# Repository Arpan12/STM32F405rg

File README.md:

a STM32 based board designed in Kicad. Have support for UART,I2C. Firmware can be uploaded using SWD pin. Support for debugging using SWO. Can be powered by 12v or 5v USB.

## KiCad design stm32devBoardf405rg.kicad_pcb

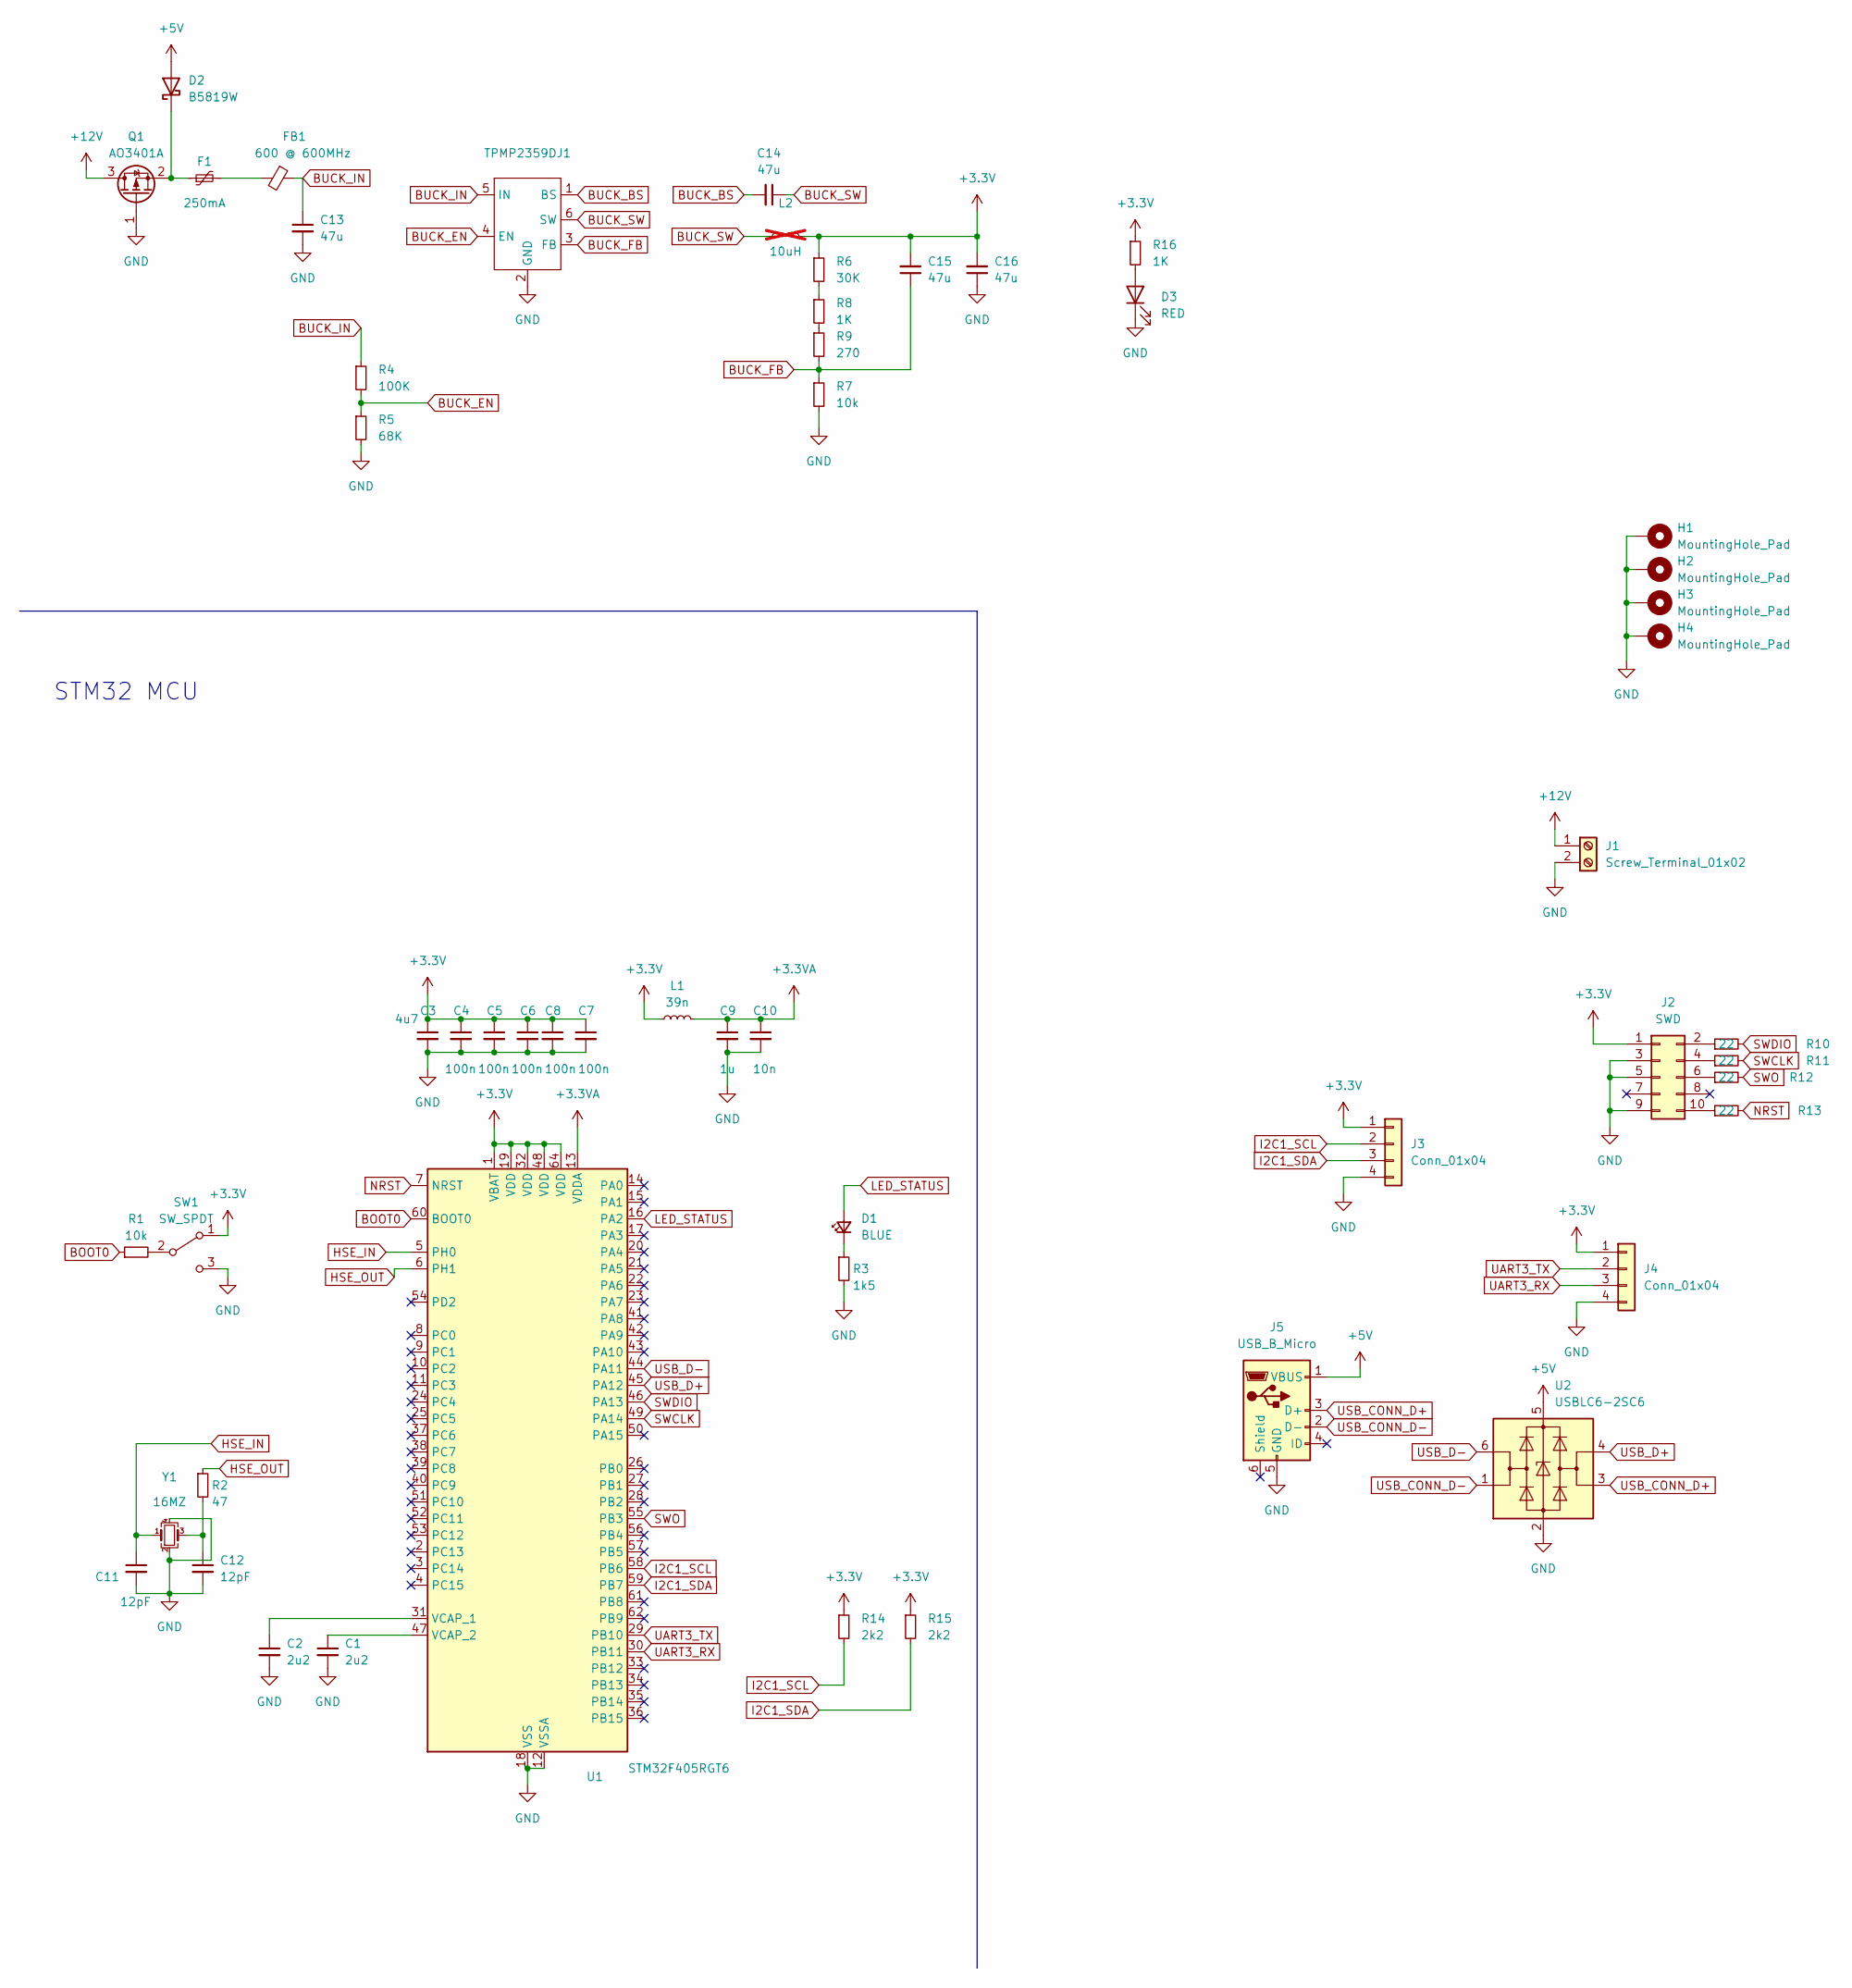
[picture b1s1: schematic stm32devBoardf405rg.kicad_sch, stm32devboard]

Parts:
C1, C2: 2u2; C_0603_1608Metric; LCSC Part# C23630
C3: 4u7; C_0603_1608Metric; LCSC Part# C19666
C4, C5, C6, C7, C8: 100n; C_0402_1005Metric; LCSC Part# C1525
C9: 1u; C_0402_1005Metric; LCSC Part# C52923
C10: 10n; C_0402_1005Metric; LCSC Part# C15195
C11, C12: 12pF; C_0402_1005Metric; LCSC Part# C1547
C13, C14, C15, C16: 47u; C_0603_1608Metric; LCSC Part# C178330
D1: BLUE; LED_0603_1608Metric; LCSC Part# C72041
D2: B5819W; D_SOD-123; LCSC Part# C8598
D3: RED; LED_0603_1608Metric; LCSC Part# C2286
F1: 250mA; Fuse_1206_3216Metric; LCSC Part# C369159
FB1: 600 @ 600MHz; L_0805_2012Metric; LCSC Part# C1017
H1, H2, H3, H4: MountingHole_Pad; MountingHole_4.3mm_M4_Pad_Via
J1: Screw_Terminal_01x02; TerminalBlock_Phoenix_PT-1,5-2-3.5-H_1x02_P3.50mm_Horizontal
J2: SWD; PinHeader_2x05_P1.27mm_Vertical_SMD
J3, J4: Conn_01x04; Molex_PicoBlade_53048-0410_1x04_P1.25mm_Horizontal
J5: USB_B_Micro; USB_Micro-B_Amphenol_10103594-0001LF_Horizontal
L1: 39n; C_0402_1005Metric; LCSC Part# C26443
L2: 10uH; L_Sunlord_MWSA0503S; LCSC Part# C139506; not fitted
Q1: AO3401A; SOT-23; LCSC Part# C15127
R1: 10k; R_0402_1005Metric; LCSC Part# C25744
R2: 47; R_0402_1005Metric; LCSC Part# C25118
R3: 1k5; R_0603_1608Metric; LCSC Part# C22843
R4: 100K; R_0603_1608Metric; LCSC Part# C25803
R5: 68K; R_0603_1608Metric; LCSC Part# C23231
R6: 30K; R_0603_1608Metric; LCSC Part# C22984
R7: 10k; R_0603_1608Metric; LCSC Part# C25804
R8, R16: 1K; R_0603_1608Metric; LCSC Part# C21190
R9: 270; R_0603_1608Metric; LCSC Part# C22966
R10, R11, R12, R13: 22; R_0603_1608Metric; LCSC Part# C23345
R14, R15: 2k2; R_0402_1005Metric; LCSC Part# C25879
SW1: SW_SPDT; SW_SPDT_PCM12
TPMP2359DJ1: SOT-23-6; LCSC Part# C2959845
U1: STM32F405RGT6; LQFP-64_10x10mm_P0.5mm; LCSC Part# C15742
U2: USBLC6-2SC6; SOT-23-6; LCSC Part# C7519
Y1: 16MZ; Crystal_SMD_3225-4Pin_3.2x2.5mm; LCSC Part# C13738

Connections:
+3.3V: C3.1, C4.1, C5.1, C6.1, C7.1, C8.1, C15.2, C16.2, J2.1, J3.1, J4.1, L1.1, L2.2, R6.1, R14.1, R15.1, R16.1, SW1.1 (A), U1.1 (VBAT), U1.19 (VDD), U1.32 (VDD), U1.48 (VDD), U1.64 (VDD)
+3.3VA: C9.1, C10.1, L1.2, U1.13 (VDDA)
+5V: D2.2 (A), J5.1 (VBUS), U2.5 (VBUS)
+12V: J1.1, Q1.3 (D)
BOOT0: R1.1, U1.60 (BOOT0)
BUCK_BS: C14.2, TPMP2359DJ1.1 (BS)
BUCK_EN: R4.2, R5.1, TPMP2359DJ1.4 (EN)
BUCK_FB: C15.1, R7.1, R9.2, TPMP2359DJ1.3 (FB)
BUCK_IN: C13.1, FB1.1, R4.1, TPMP2359DJ1.5 (IN)
BUCK_SW: C14.1, L2.1, TPMP2359DJ1.6 (SW)
GND: C1.2, C2.2, C3.2, C4.2, C5.2, C6.2, C7.2, C8.2, C9.2, C10.2, C11.2, C12.2, C13.2, C16.1, D3.1 (K), H1.1, H2.1, H3.1, H4.1, J1.2, J2.3, J2.5, J2.9, J3.4, J4.4, J5.5 (GND), Q1.1 (G), R3.2, R5.2, R7.2, SW1.3 (C), TPMP2359DJ1.2 (GND), U1.12 (VSSA), U1.18 (VSS), U1.63 (VSS), U2.2 (GND), Y1.2, Y1.4
HSE_IN: C11.1, U1.5 (PH0), Y1.1
HSE_OUT: R2.1, U1.6 (PH1)
I2C1_SCL: J3.2, R14.2, U1.58 (PB6)
I2C1_SDA: J3.3, R15.2, U1.59 (PB7)
LED_STATUS: D1.2 (A), U1.16 (PA2)
NRST: R13.2, U1.7 (NRST)
unnamed: C12.1, R2.2, Y1.3
unnamed: D1.1 (K), R3.1
unnamed: D2.1 (K), F1.1, Q1.2 (S)
unnamed: D3.2 (A), R16.2
unnamed: F1.2, FB1.2
unnamed: J2.2, R10.1
unnamed: J2.4, R11.1
unnamed: J2.6, R12.1
unnamed: J2.10, R13.1
unnamed: R6.2, R8.1
unnamed: R8.2, R9.1
unnamed: R1.2, SW1.2 (B)
unnamed: C2.1, U1.31 (VCAP_1)
unnamed: C1.1, U1.47 (VCAP_2)
SWCLK: R11.2, U1.49 (PA14)
SWDIO: R10.2, U1.46 (PA13)
SWO: R12.2, U1.55 (PB3)
UART3_RX: J4.3, U1.30 (PB11)
UART3_TX: J4.2, U1.29 (PB10)
USB_CONN_D+: J5.3 (D+), U2.3 (I/O2)
USB_CONN_D-: J5.2 (D-), U2.1 (I/O1)
USB_D+: U1.45 (PA12), U2.4 (I/O2)
USB_D-: U1.44 (PA11), U2.6 (I/O1)

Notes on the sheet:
STM32 MCU

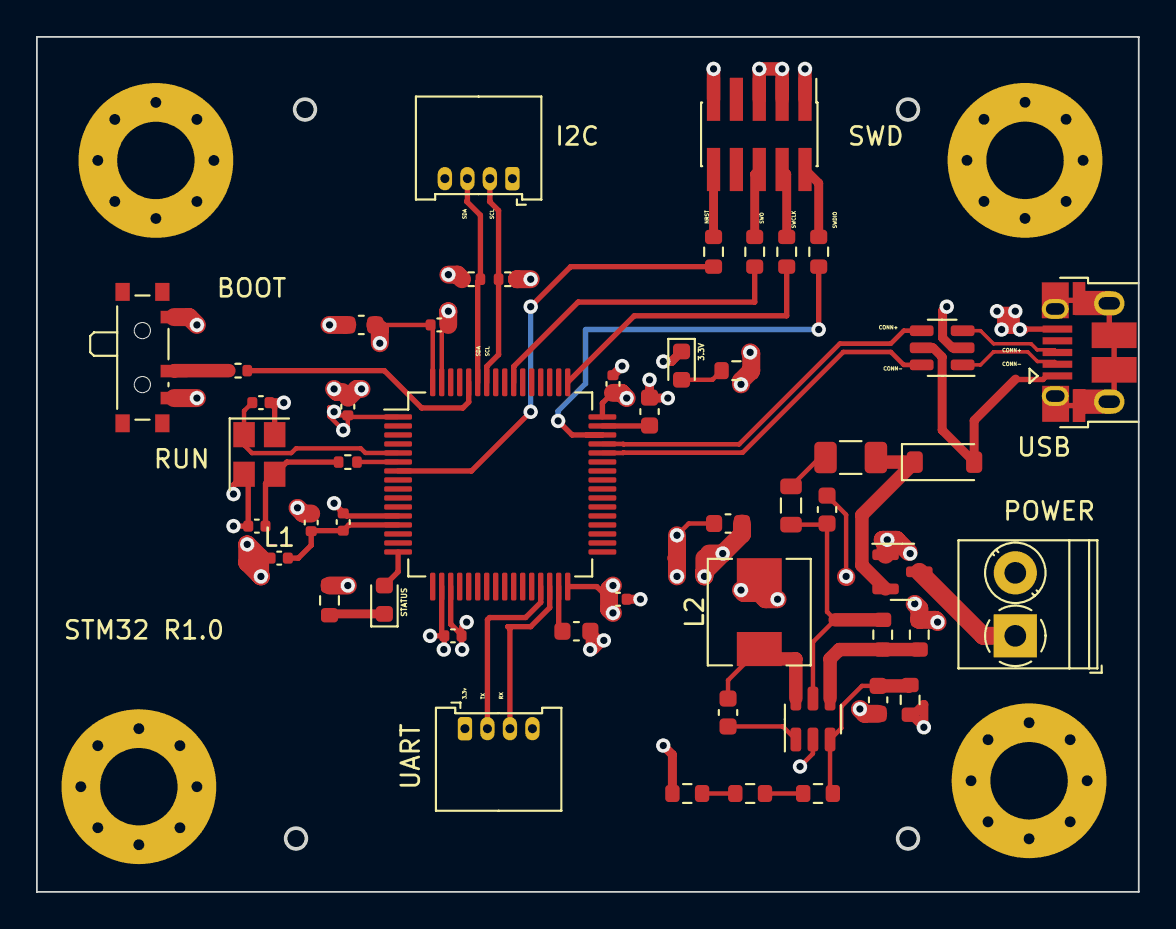
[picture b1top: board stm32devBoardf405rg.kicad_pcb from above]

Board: 4 copper layers, 61.1 x 47.4 mm, 54 parts (0 on the bottom side), 40 nets.

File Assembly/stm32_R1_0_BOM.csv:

"Reference","Value","Footprint","LCSC Part#"
"C1","2u2","Capacitor_SMD:C_0603_1608Metric","C23630"
"C2","2u2","Capacitor_SMD:C_0603_1608Metric","C23630"
"C3","4u7","Capacitor_SMD:C_0603_1608Metric","C19666"
"C4","100n","Capacitor_SMD:C_0402_1005Metric","C1525"
"C5","100n","Capacitor_SMD:C_0402_1005Metric","C1525"
"C6","100n","Capacitor_SMD:C_0402_1005Metric","C1525"
"C7","100n","Capacitor_SMD:C_0402_1005Metric","C1525"
"C8","100n","Capacitor_SMD:C_0402_1005Metric","C1525"
"C9","1u","Capacitor_SMD:C_0402_1005Metric","C52923"
"C10","10n","Capacitor_SMD:C_0402_1005Metric","C15195"
"C11","12pF","Capacitor_SMD:C_0402_1005Metric","C1547"
"C12","12pF","Capacitor_SMD:C_0402_1005Metric","C1547"
"C13","47u","Capacitor_SMD:C_0603_1608Metric","C178330"
"C14","47u","Capacitor_SMD:C_0603_1608Metric","C178330"
"C15","47u","Capacitor_SMD:C_0603_1608Metric","C178330"
"C16","47u","Capacitor_SMD:C_0603_1608Metric","C178330"
"D1","BLUE","LED_SMD:LED_0603_1608Metric","C72041"
"D2","B5819W","Diode_SMD:D_SOD-123","C8598"
"D3","RED","LED_SMD:LED_0603_1608Metric","C2286"
"F1","250mA","Fuse:Fuse_1206_3216Metric","C369159"
"FB1","600 @ 600MHz","Inductor_SMD:L_0805_2012Metric","C1017"
"H1","MountingHole_Pad","MountingHole:MountingHole_4.3mm_M4_Pad_Via",""
"H2","MountingHole_Pad","MountingHole:MountingHole_4.3mm_M4_Pad_Via",""
"H3","MountingHole_Pad","MountingHole:MountingHole_4.3mm_M4_Pad_Via",""
"H4","MountingHole_Pad","MountingHole:MountingHole_4.3mm_M4_Pad_Via",""
"J1","Screw_Terminal_01x02","TerminalBlock_Phoenix:TerminalBlock_Phoenix_PT-1,5-2-3.5-H_1x02_P3.50mm_Horizontal",""
"J2","SWD","Connector_PinHeader_1.27mm:PinHeader_2x05_P1.27mm_Vertical_SMD",""
"J3","Conn_01x04","Connector_Molex:Molex_PicoBlade_53048-0410_1x04_P1.25mm_Horizontal",""
"J4","Conn_01x04","Connector_Molex:Molex_PicoBlade_53048-0410_1x04_P1.25mm_Horizontal",""
"J5","USB_B_Micro","Connector_USB:USB_Micro-B_Amphenol_10103594-0001LF_Horizontal",""
"L1","39n","Capacitor_SMD:C_0402_1005Metric","C26443"
"L2","10uH","Inductor_SMD:L_Sunlord_MWSA0503S","C139506"
"Q1","AO3401A","Package_TO_SOT_SMD:SOT-23","C15127"
"R1","10k","Resistor_SMD:R_0402_1005Metric","C25744"
"R2","47","Resistor_SMD:R_0402_1005Metric","C25118"
"R3","1k5","Resistor_SMD:R_0603_1608Metric","C22843"
"R4","100K","Resistor_SMD:R_0603_1608Metric","C25803"
"R5","68K","Resistor_SMD:R_0603_1608Metric","C23231"
"R6","30K","Resistor_SMD:R_0603_1608Metric","C22984"
"R7","10k","Resistor_SMD:R_0603_1608Metric","C25804"
"R8","1K","Resistor_SMD:R_0603_1608Metric","C21190"
"R9","270","Resistor_SMD:R_0603_1608Metric","C22966"
"R10","22","Resistor_SMD:R_0603_1608Metric","C23345"
"R11","22","Resistor_SMD:R_0603_1608Metric","C23345"
"R12","22","Resistor_SMD:R_0603_1608Metric","C23345"
"R13","22","Resistor_SMD:R_0603_1608Metric","C23345"
"R14","2k2","Resistor_SMD:R_0402_1005Metric","C25879"
"R15","2k2","Resistor_SMD:R_0402_1005Metric","C25879"
"R16","1K","Resistor_SMD:R_0603_1608Metric","C21190"
"SW1","SW_SPDT","Button_Switch_SMD:SW_SPDT_PCM12",""
"TPMP2359DJ1","~","Package_TO_SOT_SMD:SOT-23-6","C2959845"
"U1","STM32F405RGT6","Package_QFP:LQFP-64_10x10mm_P0.5mm","C15742"
"U2","USBLC6-2SC6","Package_TO_SOT_SMD:SOT-23-6","C7519"
"Y1","16MZ","Crystal:Crystal_SMD_3225-4Pin_3.2x2.5mm","C13738 "

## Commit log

2023-11-26 MCU board schematic done
2023-11-26 added buck regulator TPMP2359 power supply
2023-11-26 added I2C
2023-11-26 USB connector
2023-11-26 USB connector II
2023-11-28 added footprint
2023-11-28 added footprint II
2023-11-28 added clearance for pcb
2023-11-28 assigned rough layout in pcb
2023-11-28 added pin no to TPMP2359 buck regulator
2023-12-04 fine placement for timer,indicator led,power decoupling capacitors,Boot pin
2023-12-05 finished with the placing of component
2023-12-05 made GND and PWR cu layer
2023-12-07 route decoupling capacitor,i2c,swd
2023-12-08 added more routes
2023-12-09 added 3.3v and grd vias
2023-12-09 fixed via routing issue
2023-12-11 corrected fill layers and added edge cuts
2023-12-11 added readme file
2023-12-11 removed unnecssary values and reference from silkscreen
2023-12-12 replaced swd footprint
2024-08-12 first STM32 board,final commit
